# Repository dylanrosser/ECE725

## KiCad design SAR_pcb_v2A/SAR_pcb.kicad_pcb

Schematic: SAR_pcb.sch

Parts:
C1, C2, C3: 10u; C_0805_2012Metric
C13, C14, C15, C17, C18, C19, C20, C21: 0.01u; C_0603_1608Metric
C16: 1u; C_0805_2012Metric
H1, H2, H3, H4: MountingHole; MountingHole_3mm
J1, J2: Conn_Coaxial_Power; BNC_TEConnectivity_1478204_Vertical
J3: Conn_02x10_Top_Bottom; PinHeader_2x10_P2.54mm_Vertical
J4: Conn_01x06; PinSocket_1x06_P2.54mm_Vertical
J9, J10: Conn_Coaxial; CustomSMA
L1: 1 nH; L_0603_1608Metric
L2: 2.2 nH; L_0603_1608Metric
R1, R8, R9: 0,<0.3 mOhm; R_0603_1608Metric
R2, R4: 49.9; R_0603_1608Metric
R3: 26.1; R_0603_1608Metric
R5: 10; R_0603_1608Metric
R6: 1k; R_0805_2012Metric
R7: 100; R_0603_1608Metric
SW1: SW_Push; SW_DIP_SPSTx02_Slide_9.78x7.26mm_W7.62mm_P2.54mm
U2: 10B_SAR; QFN-32-1EP_5x5mm_P0.5mm_EP3.1x3.1mm_ThermalVias

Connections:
CLK+: J9.1, R4.1, R5.2
CLK-: J10.1, R2.1, R3.2
CLK_FILT: R1.1, R5.1, U2.29 (CLK)
CLK_S_FILT: R3.1, U2.28 (CLK_S)
D0: J3.1, U2.24 (D0)
D1: J3.3, U2.23 (D1)
D2: J3.5, U2.22 (D2)
D3: J3.7, U2.21 (D3)
D4: J3.9, U2.20 (D4)
D5: J3.11, U2.19 (D5)
D6: J3.13, U2.18 (D6)
D7: J3.15, U2.17 (D7)
D8: J3.17, U2.15 (D8)
D9: J3.19, U2.14 (D9)
GND: C1.2, C2.2, C3.2, C13.2, C14.2, C15.2, C16.2, C17.2, C18.2, C19.2, C20.2, C21.2, J1.2, J2.2, J3.2, J3.4, J3.6, J3.8, J3.10, J3.12, J3.14, J3.16, J3.18, J3.20, J4.2, J4.4, J4.6, J9.2, J10.2, L1.2, L2.2, SW1.3, SW1.4, U2.1 (AVSS3), U2.9 (AVSS2), U2.30 (VREFM), U2.32 (AVSS1), U2.33 (GNDPD)
unnamed: L1.1, R2.2
unnamed: L2.1, R4.2
unnamed: R1.2, U2.27 (CLK_C)
RST: C16.1, R6.2, SW1.1, SW1.2, U2.13 (RST_B)
VDD: C1.1, C13.1, C17.1, C18.1, C21.1, J4.1, U2.2 (AVDD3), U2.8 (AVDD2), U2.11 (VDD1), U2.12 (VDD2), U2.25 (VDD3), U2.31 (AVDD1)
VDDPST: C2.1, C14.1, C19.1, C20.1, J4.3, R6.1, U2.10 (VDDPST2), U2.16 (VDDPST3), U2.26 (VDDPST1)
VIN+: J2.1, R7.1, U2.4 (VINP)
VIN-: J1.1, R7.2, U2.3 (VINM)
VREF: C3.1, C15.1, J4.5, U2.5 (VREFP2), U2.6 (VREFP1), U2.7 (VREFP0)

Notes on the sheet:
VDD = 0.9 V VDDPST = 1.8 V VREFP = 0.45? VREFM = 0?
Separate VREFM?
Input Elements
Output Elements
CLK TERMINATIONS
Reset Switch

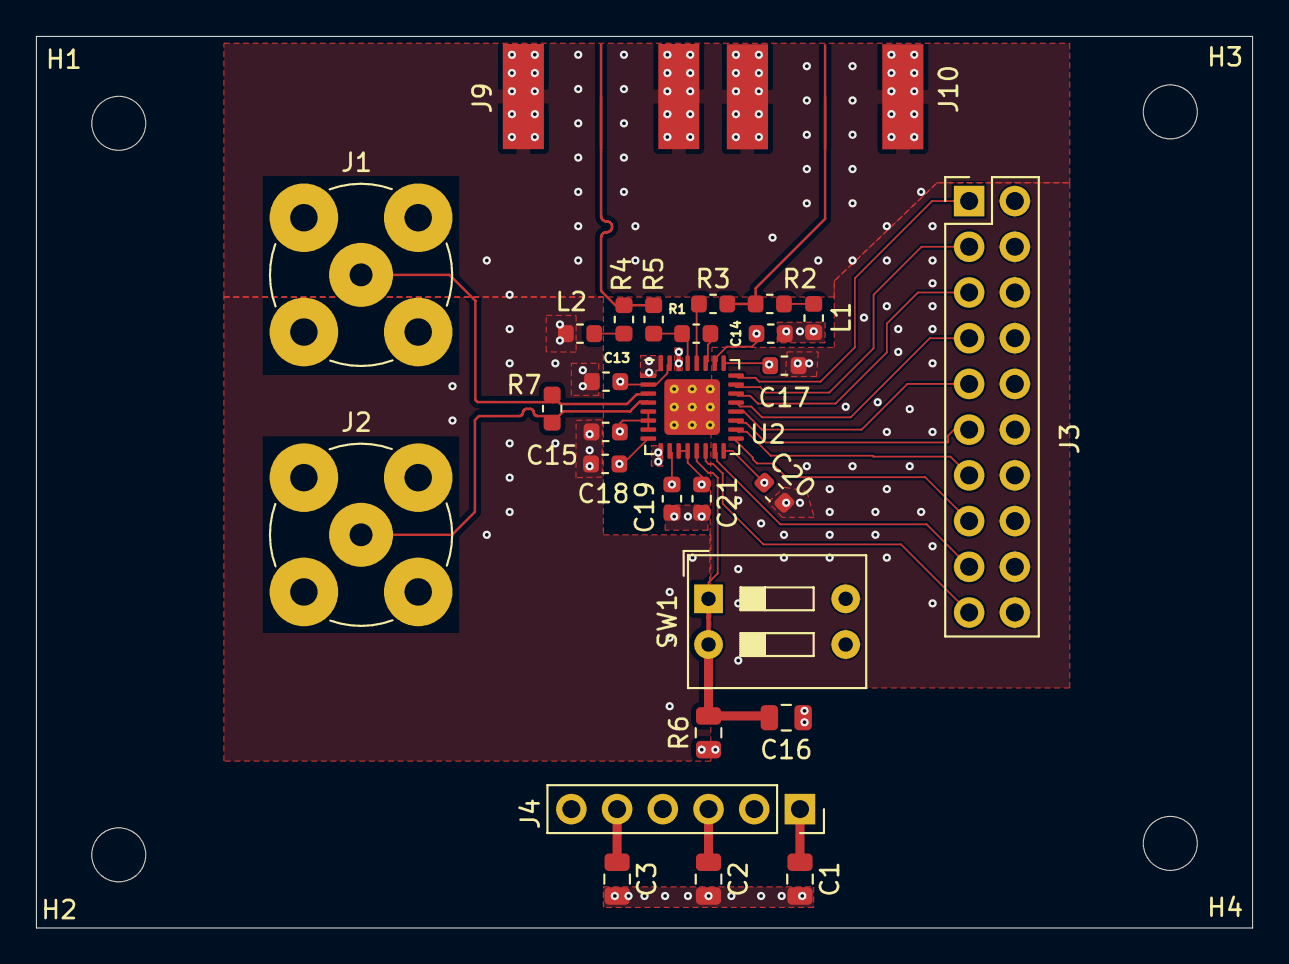
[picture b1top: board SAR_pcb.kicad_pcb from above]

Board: 4 copper layers, 67.6 x 49.5 mm, 33 parts (0 on the bottom side), 24 nets.

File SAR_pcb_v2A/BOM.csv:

"Source:","C:\Users\Dylan\Documents\Grad School stuff\S20\Digital_IC\ECE725\SAR_pcb_v2A\SAR_pcb.sch"
"Date:","10/21/2020 4:16:12 PM"
"Tool:","Eeschema (5.1.6)-1"
"Component Count:","35"
"Ref","Value","Footprint","Datasheet","Manufacturer","Vendor"
"C1","10u","Capacitor_SMD:C_0805_2012Metric","https://www.digikey.com/short/znt492","",""
"C2","10u","Capacitor_SMD:C_0805_2012Metric","https://www.digikey.com/short/znt492","",""
"C3","10u","Capacitor_SMD:C_0805_2012Metric","https://www.digikey.com/short/znt492","",""
"C13","0.01u","Capacitor_SMD:C_0603_1608Metric","https://www.digikey.com/short/znht7p","",""
"C14","0.01u","Capacitor_SMD:C_0603_1608Metric","https://www.digikey.com/short/znht7p","",""
"C15","0.01u","Capacitor_SMD:C_0603_1608Metric","https://www.digikey.com/short/znht7p","",""
"C16","1u","Capacitor_SMD:C_0805_2012Metric","https://www.digikey.com/short/znt4f2","",""
"C17","0.01u","Capacitor_SMD:C_0603_1608Metric","https://www.digikey.com/short/znht7p","",""
"C18","0.01u","Capacitor_SMD:C_0603_1608Metric","https://www.digikey.com/short/znht7p","",""
"C19","0.01u","Capacitor_SMD:C_0603_1608Metric","https://www.digikey.com/short/znht7p","",""
"C20","0.01u","Capacitor_SMD:C_0603_1608Metric","https://www.digikey.com/short/znht7p","",""
"C21","0.01u","Capacitor_SMD:C_0603_1608Metric","https://www.digikey.com/short/znht7p","",""
"H1","MountingHole","MountingHole:MountingHole_3mm","~","",""
"H2","MountingHole","MountingHole:MountingHole_3mm","~","",""
"H3","MountingHole","MountingHole:MountingHole_3mm","~","",""
"H4","MountingHole","MountingHole:MountingHole_3mm","~","",""
"J1","Conn_Coaxial_Power","Connector_Coaxial:BNC_TEConnectivity_1478204_Vertical","https://www.digikey.com/short/zn8tnn","",""
"J2","Conn_Coaxial_Power","Connector_Coaxial:BNC_TEConnectivity_1478204_Vertical","https://www.digikey.com/short/zn8tnn","",""
"J3","Conn_02x10_Top_Bottom","Connector_PinHeader_2.54mm:PinHeader_2x10_P2.54mm_Vertical","https://www.digikey.com/short/zn87b0","",""
"J4","Conn_01x06","Connector_PinSocket_2.54mm:PinSocket_1x06_P2.54mm_Vertical","https://www.digikey.com/short/zn8t4v","",""
"J9","Conn_Coaxial","SAR_pcb:CustomSMA","https://www.digikey.com/short/zn8tvt","",""
"J10","Conn_Coaxial","SAR_pcb:CustomSMA","https://www.digikey.com/short/zn8tvt","",""
"L1","1 nH","Inductor_SMD:L_0603_1608Metric","https://www.digikey.com/short/znt81t","",""
"L2","2.2 nH","Inductor_SMD:L_0603_1608Metric","https://www.digikey.com/short/znhtd8","",""
"R1","0,<0.3 mOhm","Resistor_SMD:R_0603_1608Metric","https://www.digikey.com/short/znhtqv","",""
"R2","49.9","Resistor_SMD:R_0603_1608Metric","https://www.digikey.com/short/znht5c","",""
"R3","26.1","Resistor_SMD:R_0603_1608Metric","https://www.digikey.com/short/znht2d","",""
"R4","49.9","Resistor_SMD:R_0603_1608Metric","https://www.digikey.com/short/znht5c","",""
"R5","10","Resistor_SMD:R_0603_1608Metric","https://www.digikey.com/short/znhtrd","",""
"R6","1k","Resistor_SMD:R_0805_2012Metric","https://www.digikey.com/short/zn87j1","",""
"R7","100","Resistor_SMD:R_0603_1608Metric","https://www.digikey.com/short/znhvnf","",""
"R8","0,<0.3 mOhm","Resistor_SMD:R_0603_1608Metric","https://www.digikey.com/short/znhtqv","",""
"R9","0,<0.3 mOhm","Resistor_SMD:R_0603_1608Metric","https://www.digikey.com/short/znhtqv","",""
"SW1","SW_Push","Button_Switch_THT:SW_DIP_SPSTx02_Slide_9.78x7.26mm_W7.62mm_P2.54mm","https://www.digikey.com/short/zn87mb","",""
"U2","10B_SAR","Package_DFN_QFN:QFN-32-1EP_5x5mm_P0.5mm_EP3.1x3.1mm_ThermalVias","","",""

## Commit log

2020-01-28 test
2020-02-07 Updated Gantt Chart
2020-03-13 created bonding diagrams
2020-03-16 Created pdfs for bonding diagram
2020-03-16 Added build sheet
2020-03-20 Updated bonding diagram and assembly sheet
2020-03-20 floor plan added
2020-03-27 added some comparator SNDR simulation results
2020-03-31 comparator model
2020-03-31 erf and sndr plots
2020-04-14 added to do list
2020-04-15 updated todo
2020-04-27 updated bonding diagram and build sheet
2020-04-29 added DRC failure report
2020-04-30 final pres
2020-04-30 updated presentation
2020-05-03 added conversion_calc to fix veriloga module
2020-05-03 updated conversion_calc
2020-09-16 new 32 pin bonding diagram
2020-10-05 first draft of pcb
2020-10-06 Added EP pin to SAR symbol
2020-10-07 Fixed Vin notation for differential net, switched to using 2-pin digital outputs for high speed adapter
2020-10-07 Added stackup PDF, corrected Board Setup in pcbnew
2020-10-08 Added info about pad impedance matching to schematic
2020-10-12 Added jumper resistance for feeding clk_c
2020-10-12 Finalized clock terminations, did BOM, TODO: BOM for input elements (see box)
2020-10-12 Updated footprints from 0805 handsolder to regular 0805
2020-10-12 Added components for decoupling caps
2020-10-14 added reset switch
2020-10-14 first draft of layout
2020-10-14 Updated schematic to use female header pins for VDD, VDDPST, etc., finalized BOM (see BOM.csv), updated footprints
2020-10-15 Draft 2 of Layout
2020-10-15 BOM update
2020-10-17 Backup commit for SAR PCB v2
2020-10-18 Updated BOM for 0603 components
2020-10-18 Updated PCB to conform to Vanessa's recommendations
2020-10-19 Added input termination
2020-10-19 Made copy of v2 PCB without 50 Ohm terminations
2020-10-19 removed via causing DRC error. fixed 90 degree angle in clock routing for v2B and rematched the track lengths
2020-10-21 update BOM and gerber files
2020-10-21 digikey car
2020-11-26 Revised to account for manufacturing issue
2021-01-16 test data
2021-01-16 Histogram for Chip B1
2021-01-16 more histogram data
2021-01-16 saved the waveforms setup for histogram tests
2021-01-16 new histogram - fine
2021-01-22 tested board A1
2021-02-15 Feb 14 Tests
2021-02-15 Matlab script for fitting TF
2021-02-15 added the fig as svg
2021-02-15 matlab for sndr
2021-02-15 added tests for today word doc
2021-02-16 ENOB vs Vcm
2021-02-16 enob vs fin
2021-02-16 Feb15
2021-02-16 enob vs fs
2021-02-19 rearranged folder
2021-02-19 VREF parsitics
2021-02-19 simulation images
2021-02-19 added more images
2021-02-19 more images
2021-02-19 matlab images
